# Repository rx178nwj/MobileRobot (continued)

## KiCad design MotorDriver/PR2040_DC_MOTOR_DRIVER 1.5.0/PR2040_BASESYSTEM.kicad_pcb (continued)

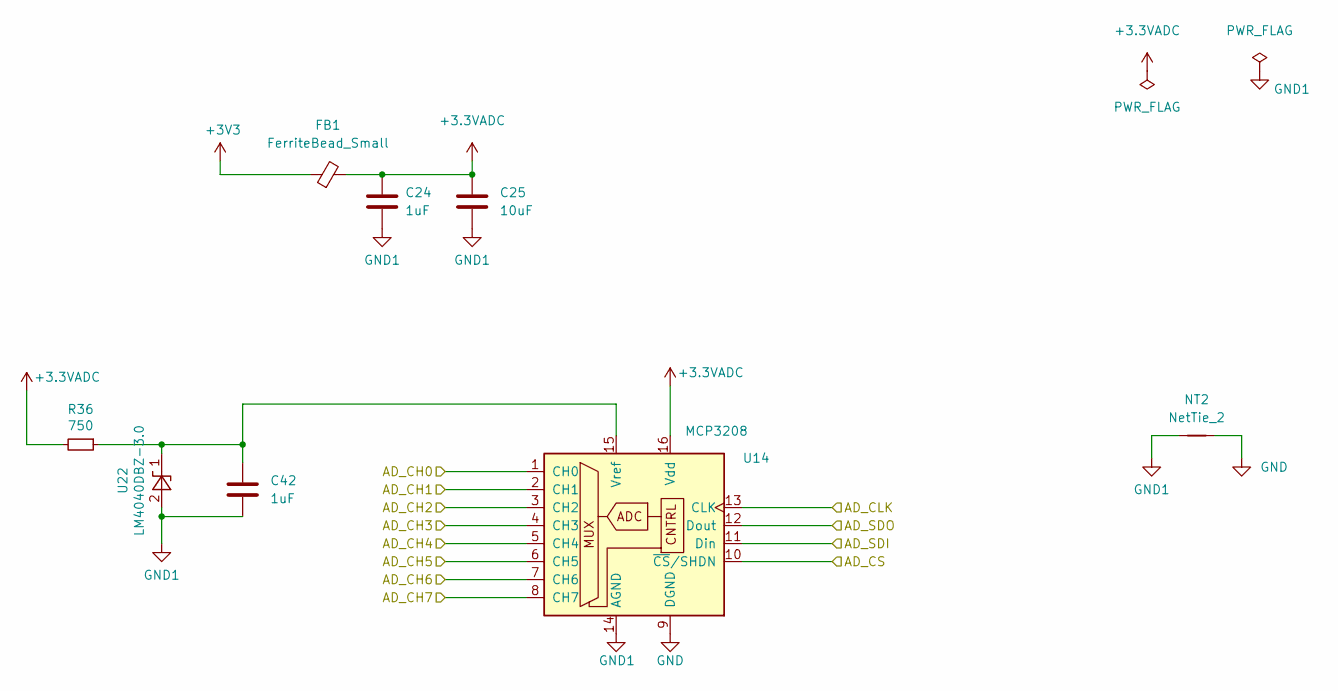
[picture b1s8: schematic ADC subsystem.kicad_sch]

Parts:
C24: 1uF; C_0603_1608Metric
C25: 10uF; C_0805_2012Metric
C42: 1uF; C_0805_2012Metric
FB1: FerriteBead_Small; L_0603_1608Metric
NT2: NetTie_2; NetTie-2_SMD_Pad0.5mm
R36: 750; R_0402_1005Metric
U14: MCP3208; SOP-16_3.9x9.9mm_P1.27mm
U22: LM4040DBZ-3.0; SOT-23

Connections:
+3.3VADC: C24.1, C25.1, FB1.2, R36.2, U14.16 (Vdd)
/AD_CH0: U14.1 (CH0); also elsewhere on the board
/AD_CH1: U14.2 (CH1); also elsewhere on the board
/AD_CH2: U14.3 (CH2); also elsewhere on the board
/AD_CH3: U14.4 (CH3); also elsewhere on the board
/AD_CH4: U14.5 (CH4); also elsewhere on the board
/AD_CH5: U14.6 (CH5); also elsewhere on the board
/AD_CH6: U14.7 (CH6); also elsewhere on the board
/AD_CH7: U14.8 (CH7); also elsewhere on the board
/SPI0_CLK: U14.13 (CLK); also elsewhere on the board
/SPI0_Cn: U14.10 (~CS/SHDN); also elsewhere on the board
/SPI0_RX: U14.12 (Dout); also elsewhere on the board
/SPI0_TX: U14.11 (Din); also elsewhere on the board
GND: NT2.2, U14.9 (DGND); also elsewhere on the board
GND1: C24.2, C25.2, C42.2, NT2.1, U14.14 (AGND), U22.2 (A)
unnamed: C42.1, R36.1, U14.15 (Vref), U22.1 (K)

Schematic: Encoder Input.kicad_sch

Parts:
C64, C65, C66, C67: 0.1u; C_0603_1608Metric
J2, J8, J9, J10: Conn_01x04_Male; JST_PH_B4B-PH-K_1x04_P2.00mm_Vertical
R23, R24, R27, R28, R41, R42, R43, R44, R54, R55, R57, R66, R67, R68, R69, R70: 10k; R_0603_1608Metric
R45, R46, R47, R48, R49, R50, R51, R52: 33; R_0603_1608Metric

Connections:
/GPIO18: R46.1; also elsewhere on the board
/GPIO19: R45.1; also elsewhere on the board
/GPIO20: R48.1; also elsewhere on the board
/GPIO21: R47.1; also elsewhere on the board
/GPIO22: R50.1; also elsewhere on the board
/GPIO23: R49.1; also elsewhere on the board
/GPIO24: R52.1; also elsewhere on the board
/GPIO25: R51.1; also elsewhere on the board
GND: C64.2, C65.2, C66.2, C67.2, J2.4, J8.4, J9.4, J10.4, R54.2, R55.2, R57.2, R66.2, R67.2, R68.2, R69.2, R70.2; also elsewhere on the board
unnamed: J2.1, R43.2, R46.2, R68.1
unnamed: J2.2, R27.2, R45.2, R55.1
unnamed: J8.1, R44.2, R48.2, R69.1
unnamed: J8.2, R28.2, R47.2, R57.1
unnamed: J9.1, R41.2, R50.2, R70.1
unnamed: J9.2, R23.2, R49.2, R66.1
unnamed: J10.1, R42.2, R52.2, R67.1
unnamed: J10.2, R24.2, R51.2, R54.1

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
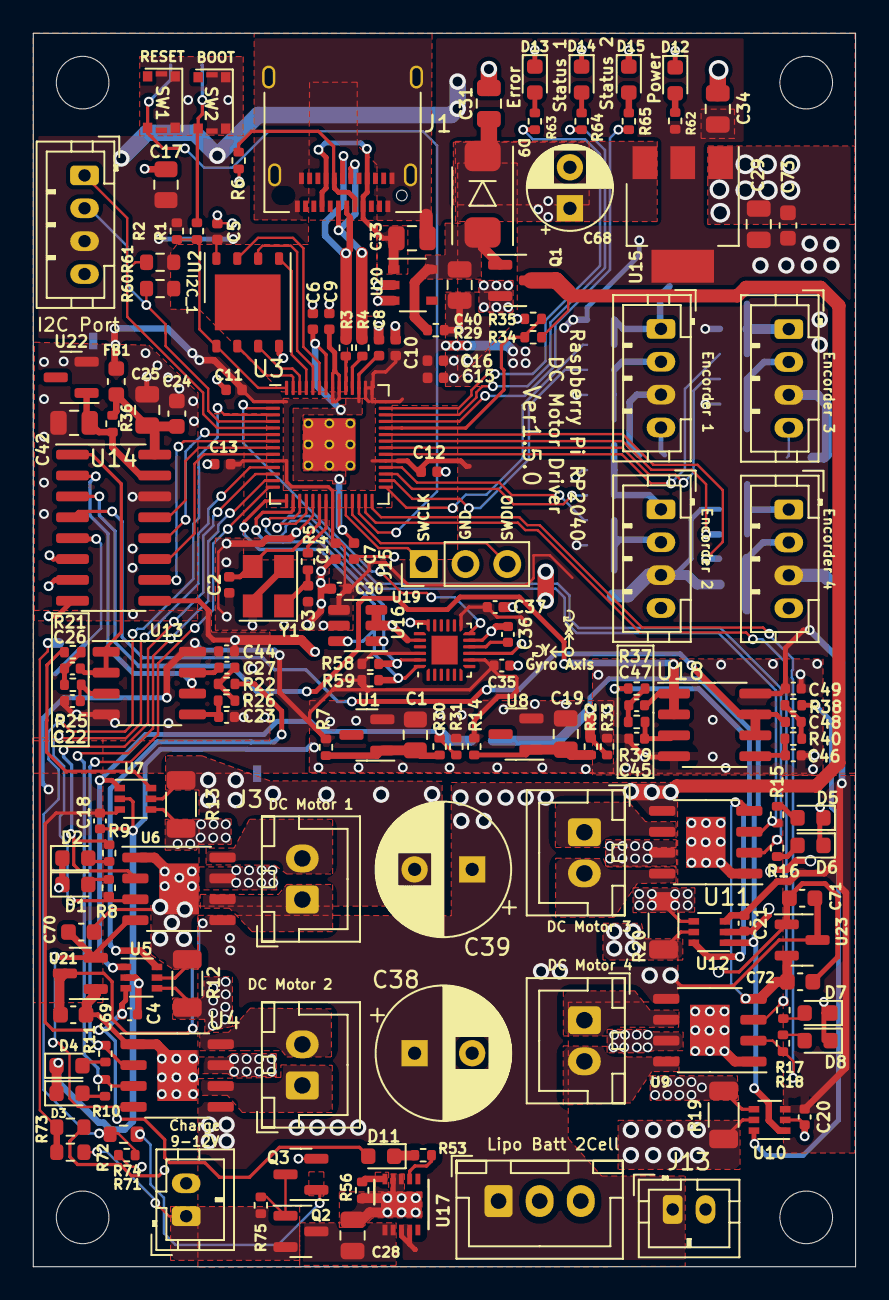
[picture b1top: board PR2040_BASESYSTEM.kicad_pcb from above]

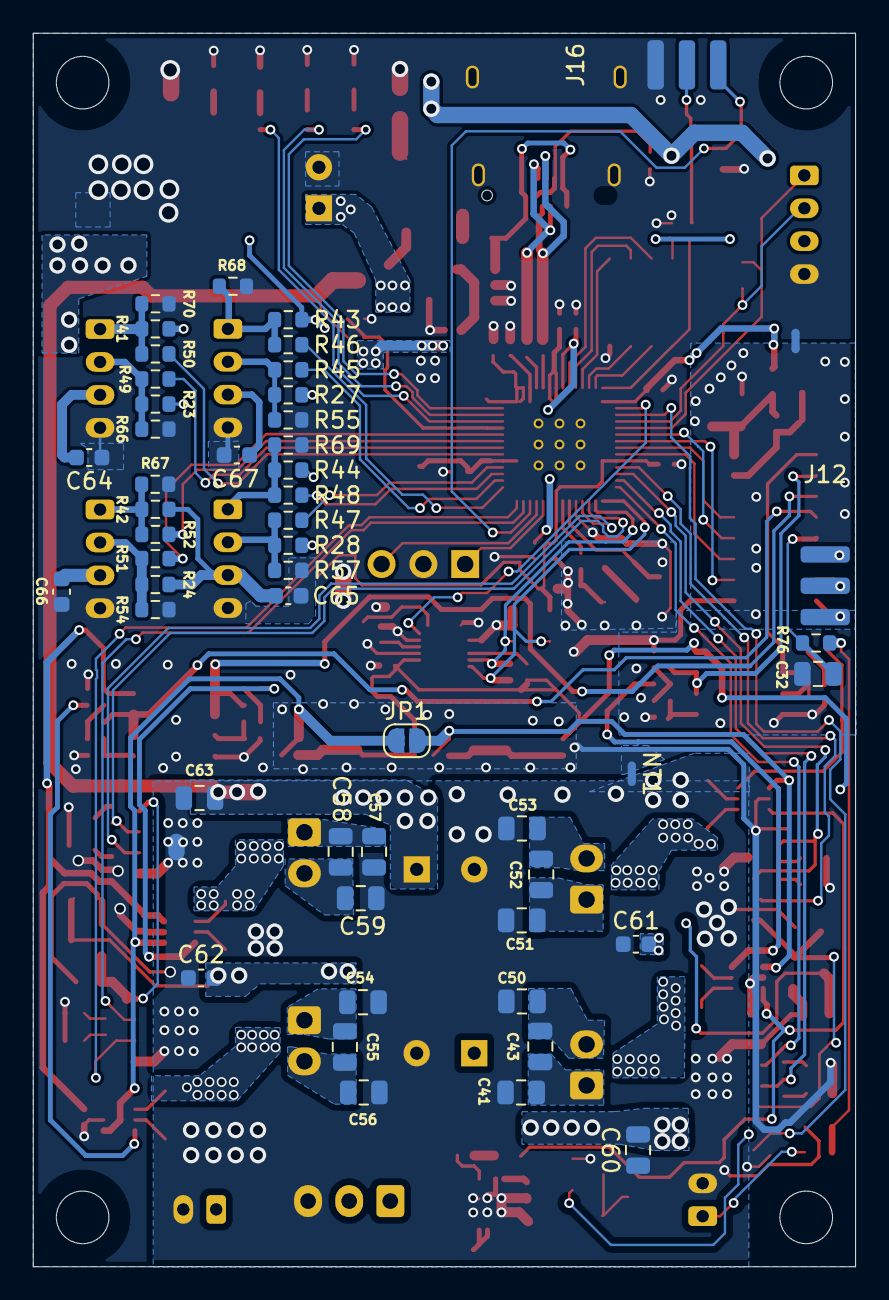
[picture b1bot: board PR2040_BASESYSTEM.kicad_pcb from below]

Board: 2 copper layers, 50.0 x 75.0 mm, 216 parts (51 on the bottom side), 126 nets.

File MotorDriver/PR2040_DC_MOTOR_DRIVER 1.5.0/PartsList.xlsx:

Reference | Value | Unit | Package |  | 数カズ | 在庫ザイコ | 購入コウニュウ | 単価タンカ |  | 合計ゴウケイ | 税込みゼイコ
> C1, C19 | 2.2uF | Capacitor_SMD | C_0805_2012Metric | ~ | 2 | o |  |  |  | 0 | 0
> C2, C3 | 27pF | Capacitor_SMD | C_0402_1005Metric | ~ | 2 |  | 10 | 6.5 | digikey | 65 | 65
> C4, C18, C20, C21, C25, C35, C36, C44, C49 | 0.1uF | Capacitor_SMD | C_0402_1005Metric | ~ | 9 |  | 200 | 2.5 | digikey | 500 | 500
> C5-C7, C9, C11-C16 | 100nF | Capacitor_SMD | C_0402_1005Metric | ~ | 10 | - | 0 | 0 |  | 0 | 0
> C8, C10 | 1uF | Capacitor_SMD | C_0402_1005Metric | ~ | 2 |  | 50 | 7.3 | digikey | 365 | 365
> C17, C24, C28, C29, C31, C34 | 10uF | Capacitor_SMD | C_0805_2012Metric | ~ | 6 | o |  |  |  | 0 | 0
> C22, C23, C26, C27, C37, C45-C48 | 10nF | Capacitor_SMD | C_0402_1005Metric | ~ | 9 |  | 100 | 1.9 | digikey | 190 | 190
> C33, C40, C42 | 1uF | Capacitor_SMD | C_0805_2012Metric | ~ | 3 | o |  |  |  | 0 | 0
> C38, C39 | 1000uF | Capacitor_THT | CP_Radial_D10.0mm_P5.00mm | ~ | 2 | o |  |  |  | 0 | 0
> D2, D4, D6, D8 | LED yellow | LED_SMD | LED_0603_1608Metric | ~ | 4 | - | 0 | 0 |  | 0 | 0
> D1, D3, D5, D7 | LED green | LED_SMD | LED_0603_1608Metric | ~ | 4 | - | 0 | 0 |  | 0 | 0
D9 | ＳＲ５４Ｆ | Diode_SMD | D_SMB | ~ | 1 |  | 10 | 25 | 秋月電子アキヅキデンシ | 250 | 275
D11 | LED | LED_SMD | LED_0603_1608Metric | ~ | 1 |  | 40 | 10 | 秋月電子アキヅキデンシ | 400 | 440
D12 | LED BLUE | LED_SMD | LED_0603_1608Metric | ~ | 1 |  | 40 | 12 | 秋月電子アキヅキデンシ | 480 | 528
D13 | LED YELLOW | LED_SMD | LED_0603_1608Metric | ~ | 1 |  | 40 | 10 | 秋月電子アキヅキデンシ | 400 | 440
D14 | LED GREEN | LED_SMD | LED_0603_1608Metric | ~ | 1 |  | 40 | 10 | 秋月電子アキヅキデンシ | 400 | 440
D15 | LED RED | LED_SMD | LED_0603_1608Metric | ~ | 1 |  | 40 | 10 | 秋月電子アキヅキデンシ | 400 | 440
> H1-H4 | MountingHole | MountingHole | MountingHole_2.7mm_M2.5 | ~ | 4 | - | 0 | 0 | - | 0 | 0
J1 | USB_C_Receptacle | Connector_USB | USB_C_Receptacle_Amphenol_12401610E4-2A | https | 1 |  | 5 | 212 | Mouser | 1060 | 1166
> J3-J7, J17 | Conn_01x02_Male | Connector_JST | JST_XH_B2B-XH-A_1x02_P2.50mm_Vertical | ~ | 6 | o | 0 | 0 |  | 0 | 0
J11 | Conn_01x03_Male | Connector_JST | JST_XH_B3B-XH-A_1x03_P2.50mm_Vertical | ~ | 1 | o | 0 | 0 |  | 0 | 0
> J2, J8-J10, J12, J13 | Conn_01x04_Male | connector_ZH | JST_ZH_B4B_ZR | ~ | 6 |  | 10 | 20 | 秋月電子アキヅキデンシ | 200 | 220
J14 | Conn_01x03_Male | connector_ZH | JST_ZH_B3B_ZR | ~ | 1 |  | 10 | 20 | 秋月電子アキヅキデンシ | 200 | 220
J15 | Conn_01x03_Male | Connector_PinHeader_2.54mm | PinHeader_1x03_P2.54mm_Vertical | ~ | 1 | o |  |  |  | 0 | 0
Q1 | DMG3415 | Package_TO_SOT_SMD | SOT-23 | ~ | 1 |  | 10 | 30 | 秋月電子アキヅキデンシ | 300 | 330
R2 | DNF | Resistor_SMD | R_0402_1005Metric | ~ | 1 | - | 0 | 0 | 0 | 0 | 0
> R3, R4 | 27 | Resistor_SMD | R_0402_1005Metric | ~ | 2 |  | 100 | 1.72 | digikey | 172 | 172
R6 | 5k | Resistor_SMD | R_0402_1005Metric | ~ | 1 |  | 100 | 0.59 | digikey | 59 | 59
> R7, R14, R36 | 100 | Resistor_SMD | R_0402_1005Metric | ~ | 3 |  | 100 | 1.83 | digikey | 183 | 183
> R12, R13, R19, R20 | 5m | Resistor_SMD | R_1206_3216Metric | ~ | 4 |  | 10 | 64.5 | digikey | 645 | 645
> R21, R22, R25, R26, R37-R40 | 16k | Resistor_SMD | R_0402_1005Metric | ~ | 8 |  | 100 | 0.8 | digikey | 80 | 80
> R30, R32, R34 | 20k | Resistor_SMD | R_0402_1005Metric | ~ | 3 |  | 100 | 3.87 | digikey | 387 | 387
> R23, R24, R27-R29, R31, R33, R35, R41-R44 | 10k | Resistor_SMD | R_0402_1005Metric | ~ | 12 | o |  |  |  | 0 | 0
> R45-R52 | 33 | Resistor_SMD | R_0402_1005Metric | ~ | 8 |  | 100 | 4.17 | digikey | 417 | 417
R56 | 1.5k | Resistor_SMD | R_0402_1005Metric | ~ | 1 |  | 100 | 2.04 | digikey | 204 | 204
> R58, R59 | 4.7k | Resistor_SMD | R_0402_1005Metric | ~ | 2 |  | 100 | 1.91 | digikey | 191 | 191
> R60, R61 | 4.7k | Resistor_SMD | R_0603_1608Metric | ~ | 2 |  | 100 | 2.12 | digikey | 212 | 212
> R1, R5, R8-R11, R15-R18, R53, R62-R65 | 1k | Resistor_SMD | R_0402_1005Metric | ~ | 15 | o |  |  |  | 0 | 0
> SW1, SW2 | SW_SKSG10 | SW_SKSGACE010 | SW_SKSGACE010 |  | 2 |  | 10 | 70.5 | Mouser | 705 | 775
> U1, U8, U22 | LM4040DBZ-3.0 | Package_TO_SOT_SMD | SOT-23 |  | 3 |  | 10 | 74.900000000000006 | Mouser | 749 | 823
U2 | W25Q128JVPIQ TR | Package_SON | WSON-8-1EP_6x5mm_P1.27mm_EP3.4x4mm |  | 1 |  | 5 | 250 | Mouser | 1250 | 1375
U3 | RP2040 | RP2040_minimal | RP2040-QFN-56 |  | 1 | o |  |  |  | 0 | 0
> U4, U6, U9, U11 | TB67H451 | Package_SO | SSOP-8_3.9x5.05mm_P1.27mm |  | 4 |  | 10 | 173 | Mouser | 1730 | 1903
> U5, U7, U10, U12 | INA214_SC70 | Package_TO_SOT_SMD | SOT-363_SC-70-6 |  | 4 | o |  |  |  | 0 | 0
U13 | MCP602 | Package_SO | SOP-8_3.9x4.9mm_P1.27mm |  | 1 | o |  |  |  | 0 | 0
U14 | MAX11135xTI | Package_DFN_QFN | TQFN-28-1EP_5x5mm_P0.5mm_EP3.25x3.25mm |  | 1 |  | 4 | 683 | Mouser | 2732 | 3005
U15 | NCP1117-3.3_SOT223 | Package_TO_SOT_SMD | SOT-223-3_TabPin2 |  | 1 |  | 10 | 30 | 秋月電子アキヅキデンシ | 300 | 330
U16 | MPU-6881 | Package_DFN_QFN | QFN-24-1EP_3x3mm_P0.4mm_EP1.75x1.6mm |  | 1 | o |  |  |  | 0 | 0
U17 | MCP73213 | Package_DFN_QFN | DFN-10-1EP_3x3mm_P0.5mm_EP1.55x2.48mm |  | 1 |  | 5 | 297 | Mouser | 1485 | 1633
U18 | MCP602 | Package_SO | SOIC-8_3.9x4.9mm_P1.27mm |  | 1 | o |  |  |  | 0 | 0
U20 | NCP360 | Package_SO | TSOP-5_1.65x3.05mm_P0.95mm |  | 1 |  | 5 | 105 | Mouser | 525 | 577
Y1 | FA-238 12MHz | Crystal | Crystal_SMD_SeikoEpson_FA238V-4Pin_3.2x2.5mm | ~ | 1 |  | 10 | 113 | Mouser | 1130 | 1243

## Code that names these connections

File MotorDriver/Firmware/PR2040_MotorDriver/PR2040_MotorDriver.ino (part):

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 * ---- Pin Assignment (from schematic) ----------------------------------------
 *
 * Motor (TB67H451 H-bridge x4)
 *   Motor1  IN1=GPIO8   IN2=GPIO9
 *   Motor2  IN1=GPIO10  IN2=GPIO11
 *   Motor3  IN1=GPIO14  IN2=GPIO15
 *   Motor4  IN1=GPIO16  IN2=GPIO17
 *
 * Encoder (Quadrature x4)
 *   Enc1  A=GPIO18  B=GPIO19
 *   Enc2  A=GPIO20  B=GPIO21
 *   Enc3  A=GPIO22  B=GPIO23
 *   Enc4  A=GPIO24  B=GPIO25
 *
 * ADC Internal (RP2040, current sensing via INA21x + LPF)
 *   CH0=GPIO26  CH1=GPIO27  CH2=GPIO28  CH3=GPIO29
 *
 * Controller I2C (I2C1 slave, addr=0x60)
 *   SDA=GPIO2  SCL=GPIO3
 *
 * IMU MPU-6881 (I2C0)
 *   INT=GPIO0  SDA=GPIO12  SCL=GPIO13
 *
 * External ADC MCP3208/MAX11125 (SPI0)
 *   MISO=GPIO4  CS=GPIO5  SCK=GPIO6  MOSI=GPIO7
 *
 * ---- Control Modes ----------------------------------------------------------
 *
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    analogReadResolution(12);

    // SPI0 for MCP3208 external ADC
    SPI.setRX(SPI0_RX_PIN);
    SPI.setSCK(SPI0_SCK_PIN);
    SPI.setTX(SPI0_TX_PIN);
    extAdc.begin();  // also sets CS pin high

    // IMU interrupt pin
    pinMode(IMU_INT_PIN, INPUT);

    // I2C0 for MPU-6881 (master)
    Wire.setSDA(I2C0_SDA_PIN);
    Wire.setSCL(I2C0_SCL_PIN);
    Wire.begin();
    Wire.setClock(400000);

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        Serial.println("Warning: S-5851A not found.");
    }

    // I2C1 for controller communication (slave, GPIO2=SDA, GPIO3=SCL)
    Wire1.setSDA(I2C1_SDA_PIN);
    Wire1.setSCL(I2C1_SCL_PIN);
    Wire1.begin(I2C_SLAVE_ADDR);
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
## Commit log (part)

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2026-04-19 Update Lider scan pattern and USB protocol docs
2026-04-19 Add remaining robot support files
2026-04-25 LiderModule: migrate ESP32-S3 flow, add validation docs and system diagrams
2026-04-29 Integrate LiderModule ROS2 scanning
2026-04-30 Rebuild SLAM 2.5D stack from requirements
2026-04-30 Stabilize SLAM 2.5D scan/pointcloud flow and test procedure
